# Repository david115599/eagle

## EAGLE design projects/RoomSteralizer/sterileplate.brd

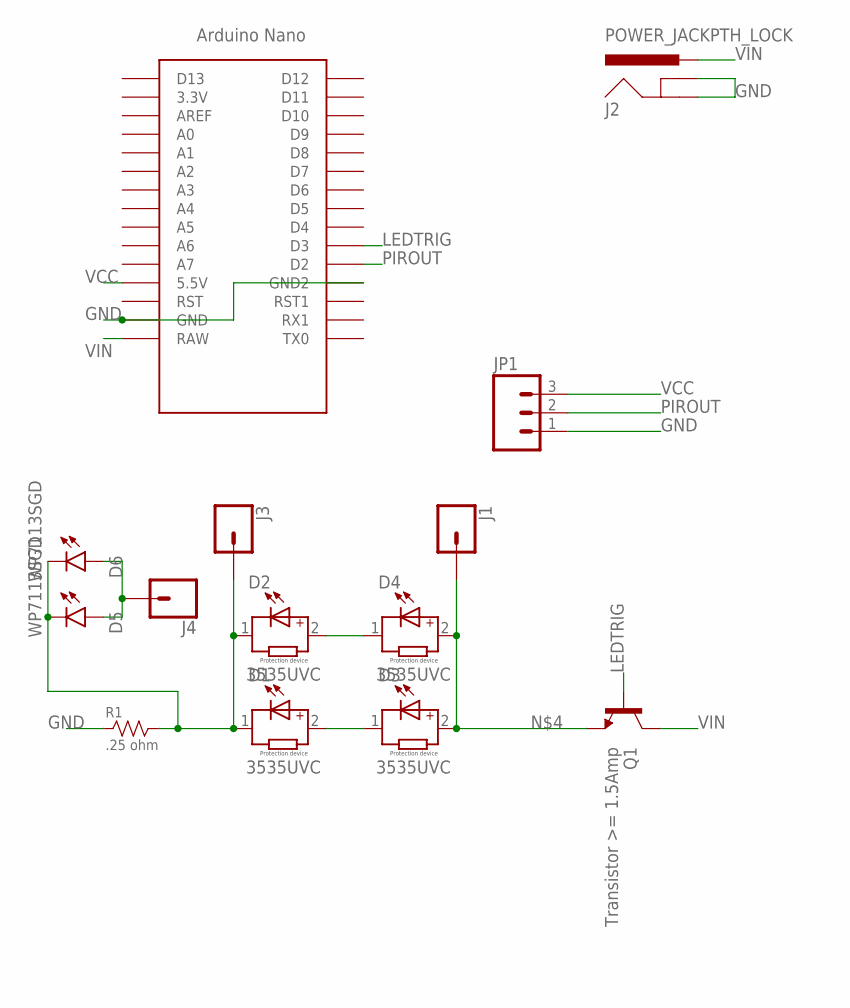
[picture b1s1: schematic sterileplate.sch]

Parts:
D1, D2, D3, D4: 3535UVC; WL-SWTC_3535
D5, D6: WP7113SGD; RADIAL_5MM
J1, J3, J4: CONN_01PTH_2MM; 1X01_2MM
J2: POWER_JACKPTH_LOCK; POWER_JACK_PTH_LOCK; MPN DCJ235-05-A-K1-K
JP1: M03PTH; 1X03
Q1: Transistor >= 1.5Amp; TO-92
R1: .25 ohm; AXL-REGULAR
U$1: NANO

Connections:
GND: J2.GND, J2.GNDBREAK, JP1.1, R1.1, U$1.GND, U$1.GND1 (GND2)
LEDTRIG: Q1.2 (B), U$1.D3
unnamed: D2.2, D4.1
unnamed: D1.2, D3.1
unnamed: D3.2, D4.2, J1.1, Q1.1 (E)
unnamed: D5.A, D6.A, J4.1
unnamed: D1.1, D2.1, D5.C, D6.C, J3.1, R1.2
PIROUT: JP1.2, U$1.D2
VCC: JP1.3, U$1.5V (5.5V)
VIN: J2.PWR, Q1.3 (C), U$1.RAW

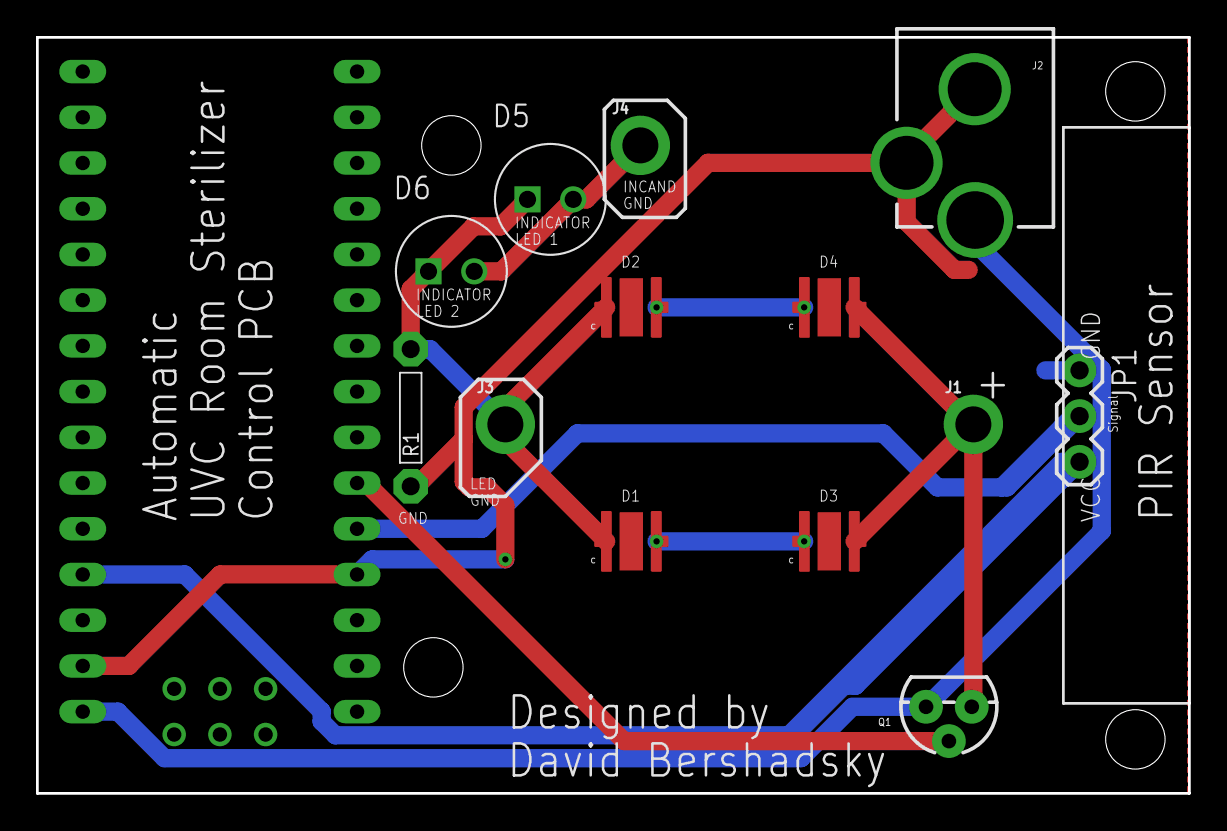
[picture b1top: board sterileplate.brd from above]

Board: 2 copper layers, 64.0 x 42.0 mm, 14 parts (0 on the bottom side), 10 nets.

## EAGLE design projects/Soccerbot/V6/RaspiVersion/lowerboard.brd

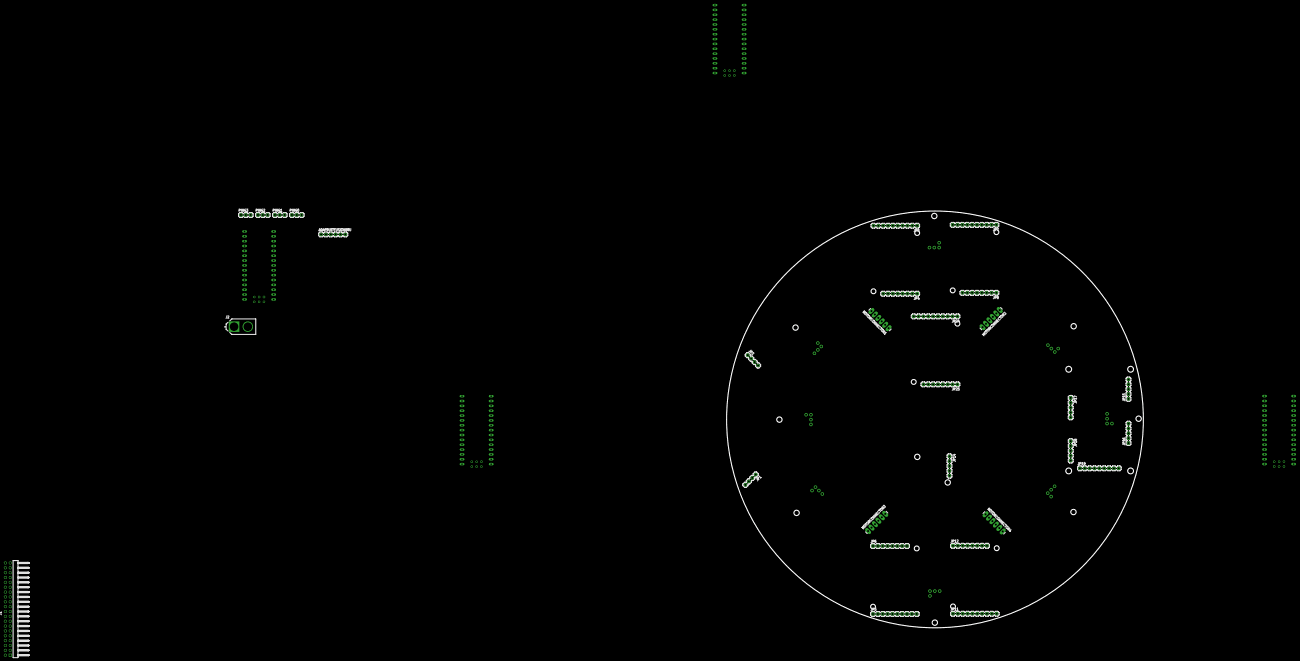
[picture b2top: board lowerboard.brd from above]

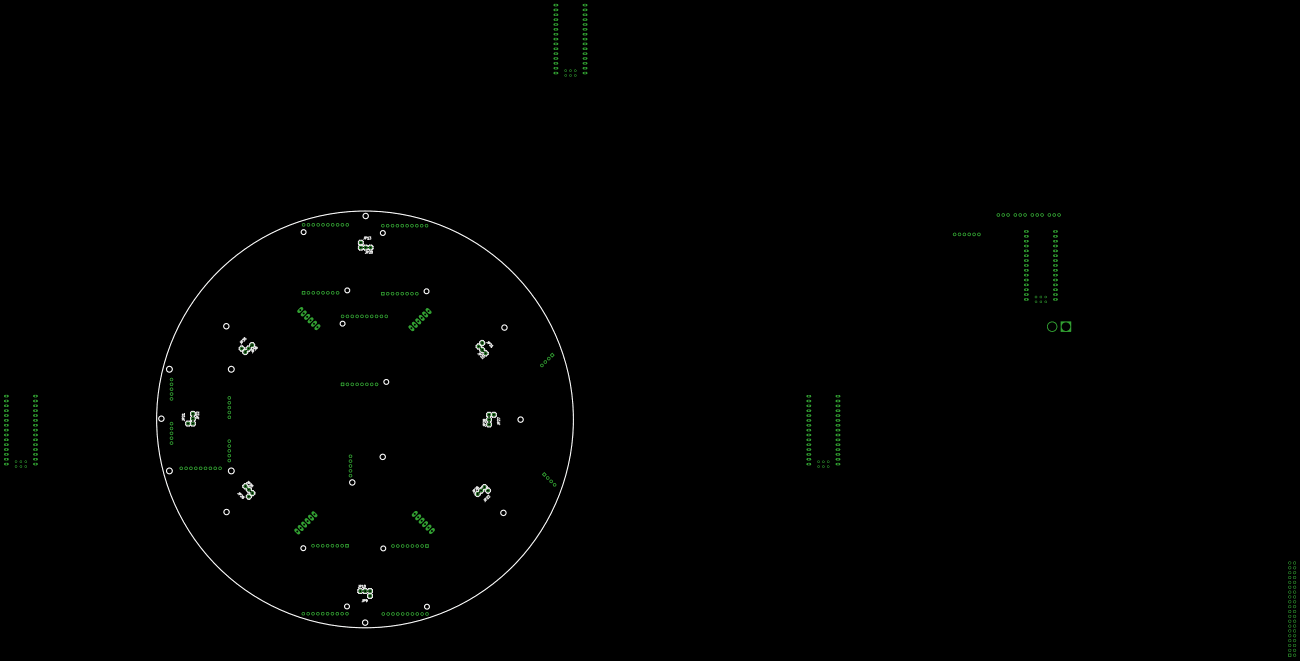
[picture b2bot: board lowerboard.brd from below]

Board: 2 copper layers, 218.0 x 218.0 mm, 49 parts (16 on the bottom side), 46 nets, no tracks yet.

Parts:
ADAFRUITFUSIONIMU: 1X06
J1: 61304021021
J2: XT60-M; AMASS_XT60-M
JP1, JP2: 1X04
JP3, JP5, JP7, JP11, JP24: M10"; 1X10
JP4, JP6, JP8, JP12, JP25: 1X08
JP9, JP13, JP21, JP23, JP27, JP29, JP31, JP35: M01PTH; 1X01
JP10, JP20, JP22, JP26, JP28, JP30, JP32, JP36: 1X03
JP14, JP15, JP16, JP17, JP18: 1X05
JP19: M09; 1X09
MOTORCONNECTOR1, MOTORCONNECTOR2, MOTORCONNECTOR3, MOTORCONNECTOR4: 1X06_LONGPADS
PING0, PING1, PING2, PING3: 1X03
U$1, U$2, U$3, U$6: NANO

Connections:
5V: JP1.4, JP2.4, JP3.7, JP5.7, JP7.7, JP10.2, JP11.7, JP14.1, JP19.8, JP20.2, JP22.2, JP24.7, JP26.2, JP28.2, JP30.2, JP32.2, JP36.2, MOTORCONNECTOR1.3, MOTORCONNECTOR2.3, MOTORCONNECTOR3.3, MOTORCONNECTOR4.3
CTRL: JP9.1, JP13.1, JP21.1, JP23.1, JP27.1, JP29.1, JP31.1, JP35.1, U$2.D2
ENCCS1: JP19.4, U$1.D2
ENCCS2: JP19.3, U$1.D3
ENCCS3: JP19.2, U$1.D4
ENCCS4: JP19.1, U$1.D5
ENCMISO: JP19.6, U$1.D12
ENCMOSI: JP19.5, U$1.D11
ENCSCLK: JP19.7, U$1.D13
GND: ADAFRUITFUSIONIMU.3, J1.5, J1.13, J1.20, J1.24, J1.26, J1.31, J1.34, J1.38, J2.1, JP1.3, JP2.3, JP3.8, JP3.10, JP4.5, JP4.6, JP5.8, JP5.10, JP6.5, JP6.6, JP7.8, JP7.10, JP8.5, JP8.6, JP10.3, JP11.8, JP11.10, JP12.5, JP12.6, JP14.2, JP14.3, JP19.9, JP20.3, JP22.3, JP24.8, JP24.10, JP25.5, JP25.6, JP26.3, JP28.3, JP30.3, JP32.3, JP36.3, MOTORCONNECTOR1.4, MOTORCONNECTOR2.4, MOTORCONNECTOR3.4, MOTORCONNECTOR4.4, PING0.1, PING1.1, PING2.1, PING3.1, U$1.GND, U$1.GND1, U$2.GND, U$2.GND1, U$3.GND, U$3.GND1, U$6.GND, U$6.GND1
INA0: JP3.1, U$6.D3
INA1: JP7.1, U$6.D7
INA2: JP5.1, U$6.D12
INA3: JP11.1, U$6.A0
INA4: JP24.1, U$6.A2
INB0: JP3.6, U$6.D4
INB1: JP7.6, U$6.D8
INB2: JP5.6, U$6.D13
INB3: JP11.6, U$6.A1
INB4: JP24.6, U$6.A3
OUTA0: JP4.1, JP4.2
OUTA1: JP8.1, JP8.2
OUTA2: JP6.1, JP6.2
OUTA3: JP12.1, JP12.2
OUTA4: JP25.1, JP25.2
OUTB0: JP4.3, JP4.4
OUTB1: JP8.3, JP8.4
OUTB2: JP6.3, JP6.4
OUTB3: JP12.3, JP12.4
OUTB4: JP25.3, JP25.4
PING0: PING0.3, U$2.A0
PING1: PING1.3, U$2.A1
PING2: PING2.3, U$2.A2
PING3: PING3.3, U$2.A3
SCLTOF: JP1.2, JP2.2, U$1.A5
SDATOF: JP1.1, JP2.1, U$1.A4
SO1: JP30.1, U$2.D3
SO2: JP22.1, U$2.D4
SO3: JP36.1, U$2.D5
SO4: JP20.1, U$2.D6
SO5: JP32.1, U$2.D7
SO6: JP28.1, U$2.D8
SO7: JP26.1, U$2.D9
VCC: ADAFRUITFUSIONIMU.1, J1.39, J1.40, PING0.2, PING1.2, PING2.2, PING3.2, U$1.5V, U$2.5V, U$3.5V, U$6.5V
VCC3.3: J1.1, J1.9, U$1.3.3V, U$2.3.3V, U$3.3.3V, U$6.3.3V
VIN: J2.2, JP4.7, JP4.8, JP6.7, JP6.8, JP8.7, JP8.8, JP12.7, JP12.8, JP14.4, JP25.7, JP25.8

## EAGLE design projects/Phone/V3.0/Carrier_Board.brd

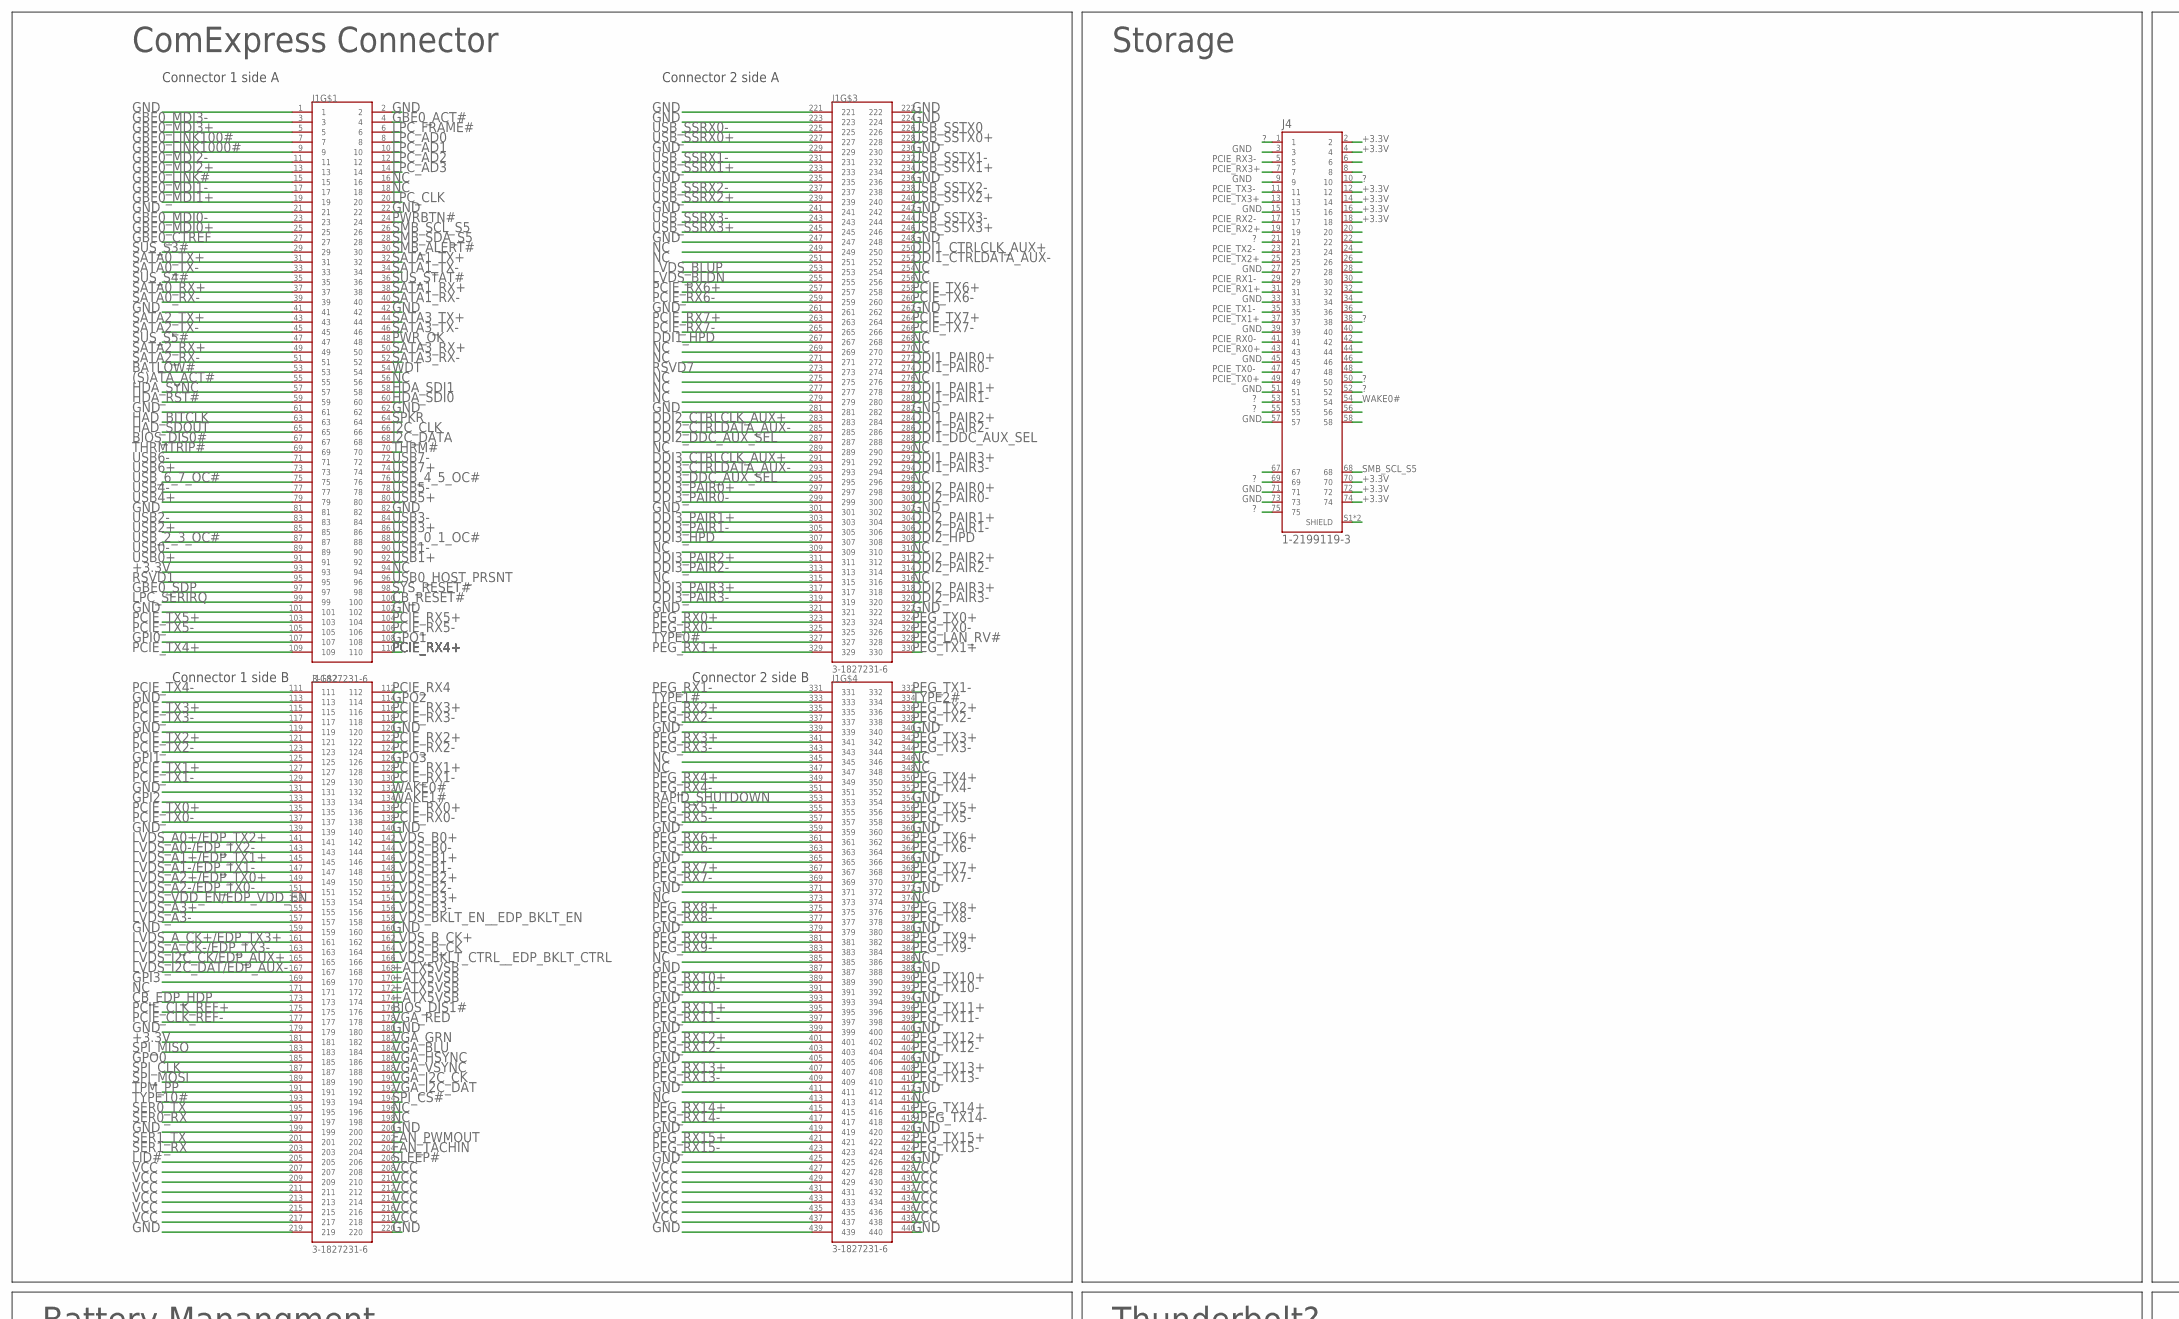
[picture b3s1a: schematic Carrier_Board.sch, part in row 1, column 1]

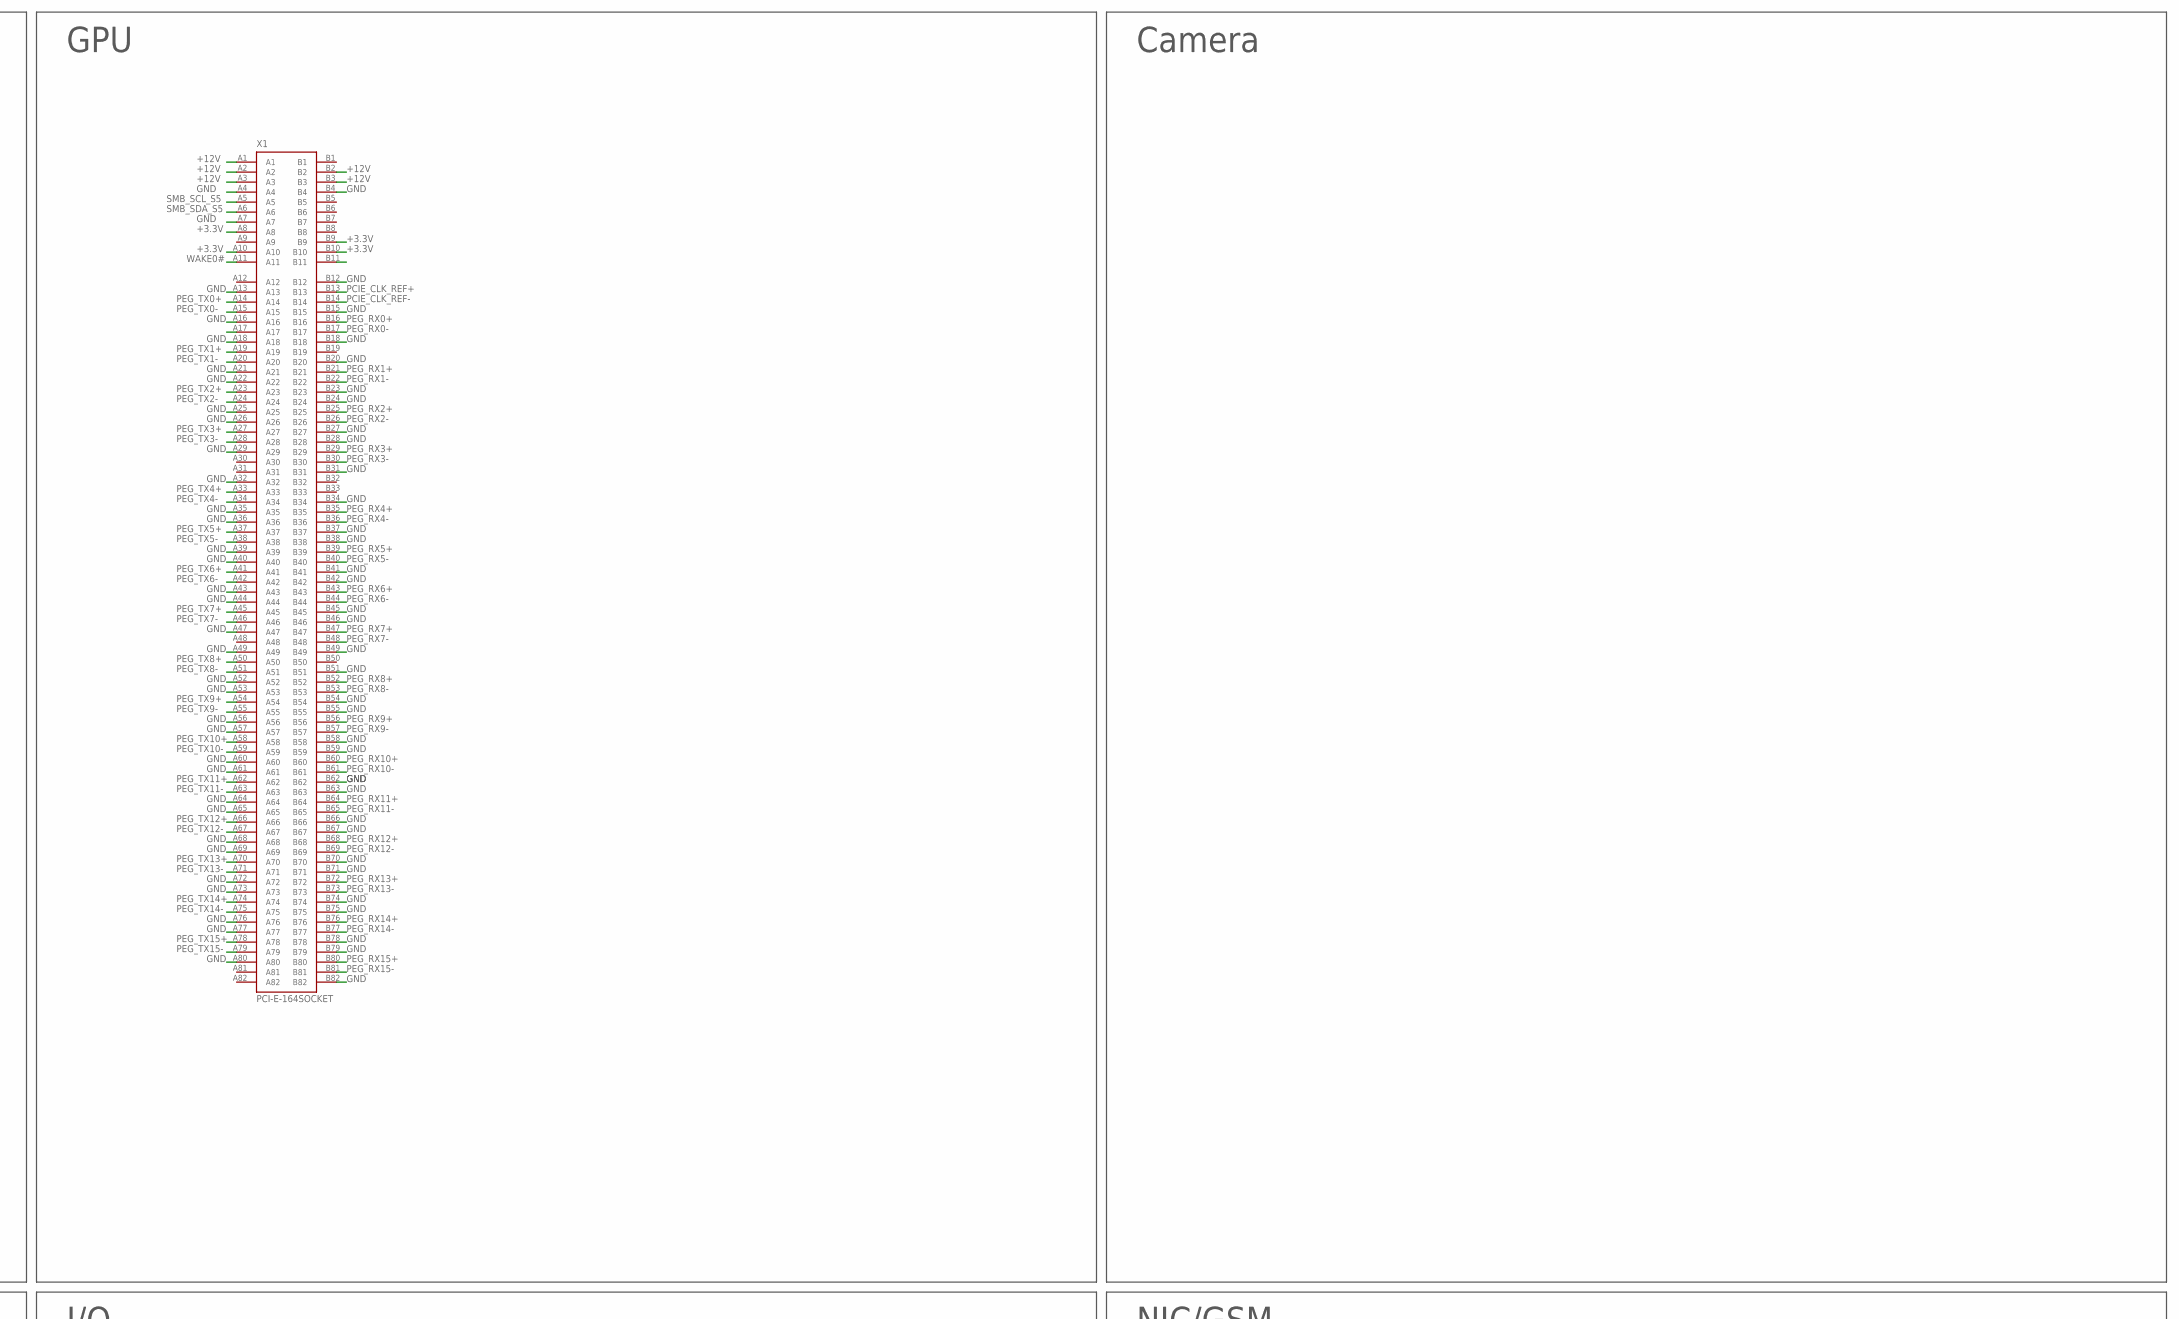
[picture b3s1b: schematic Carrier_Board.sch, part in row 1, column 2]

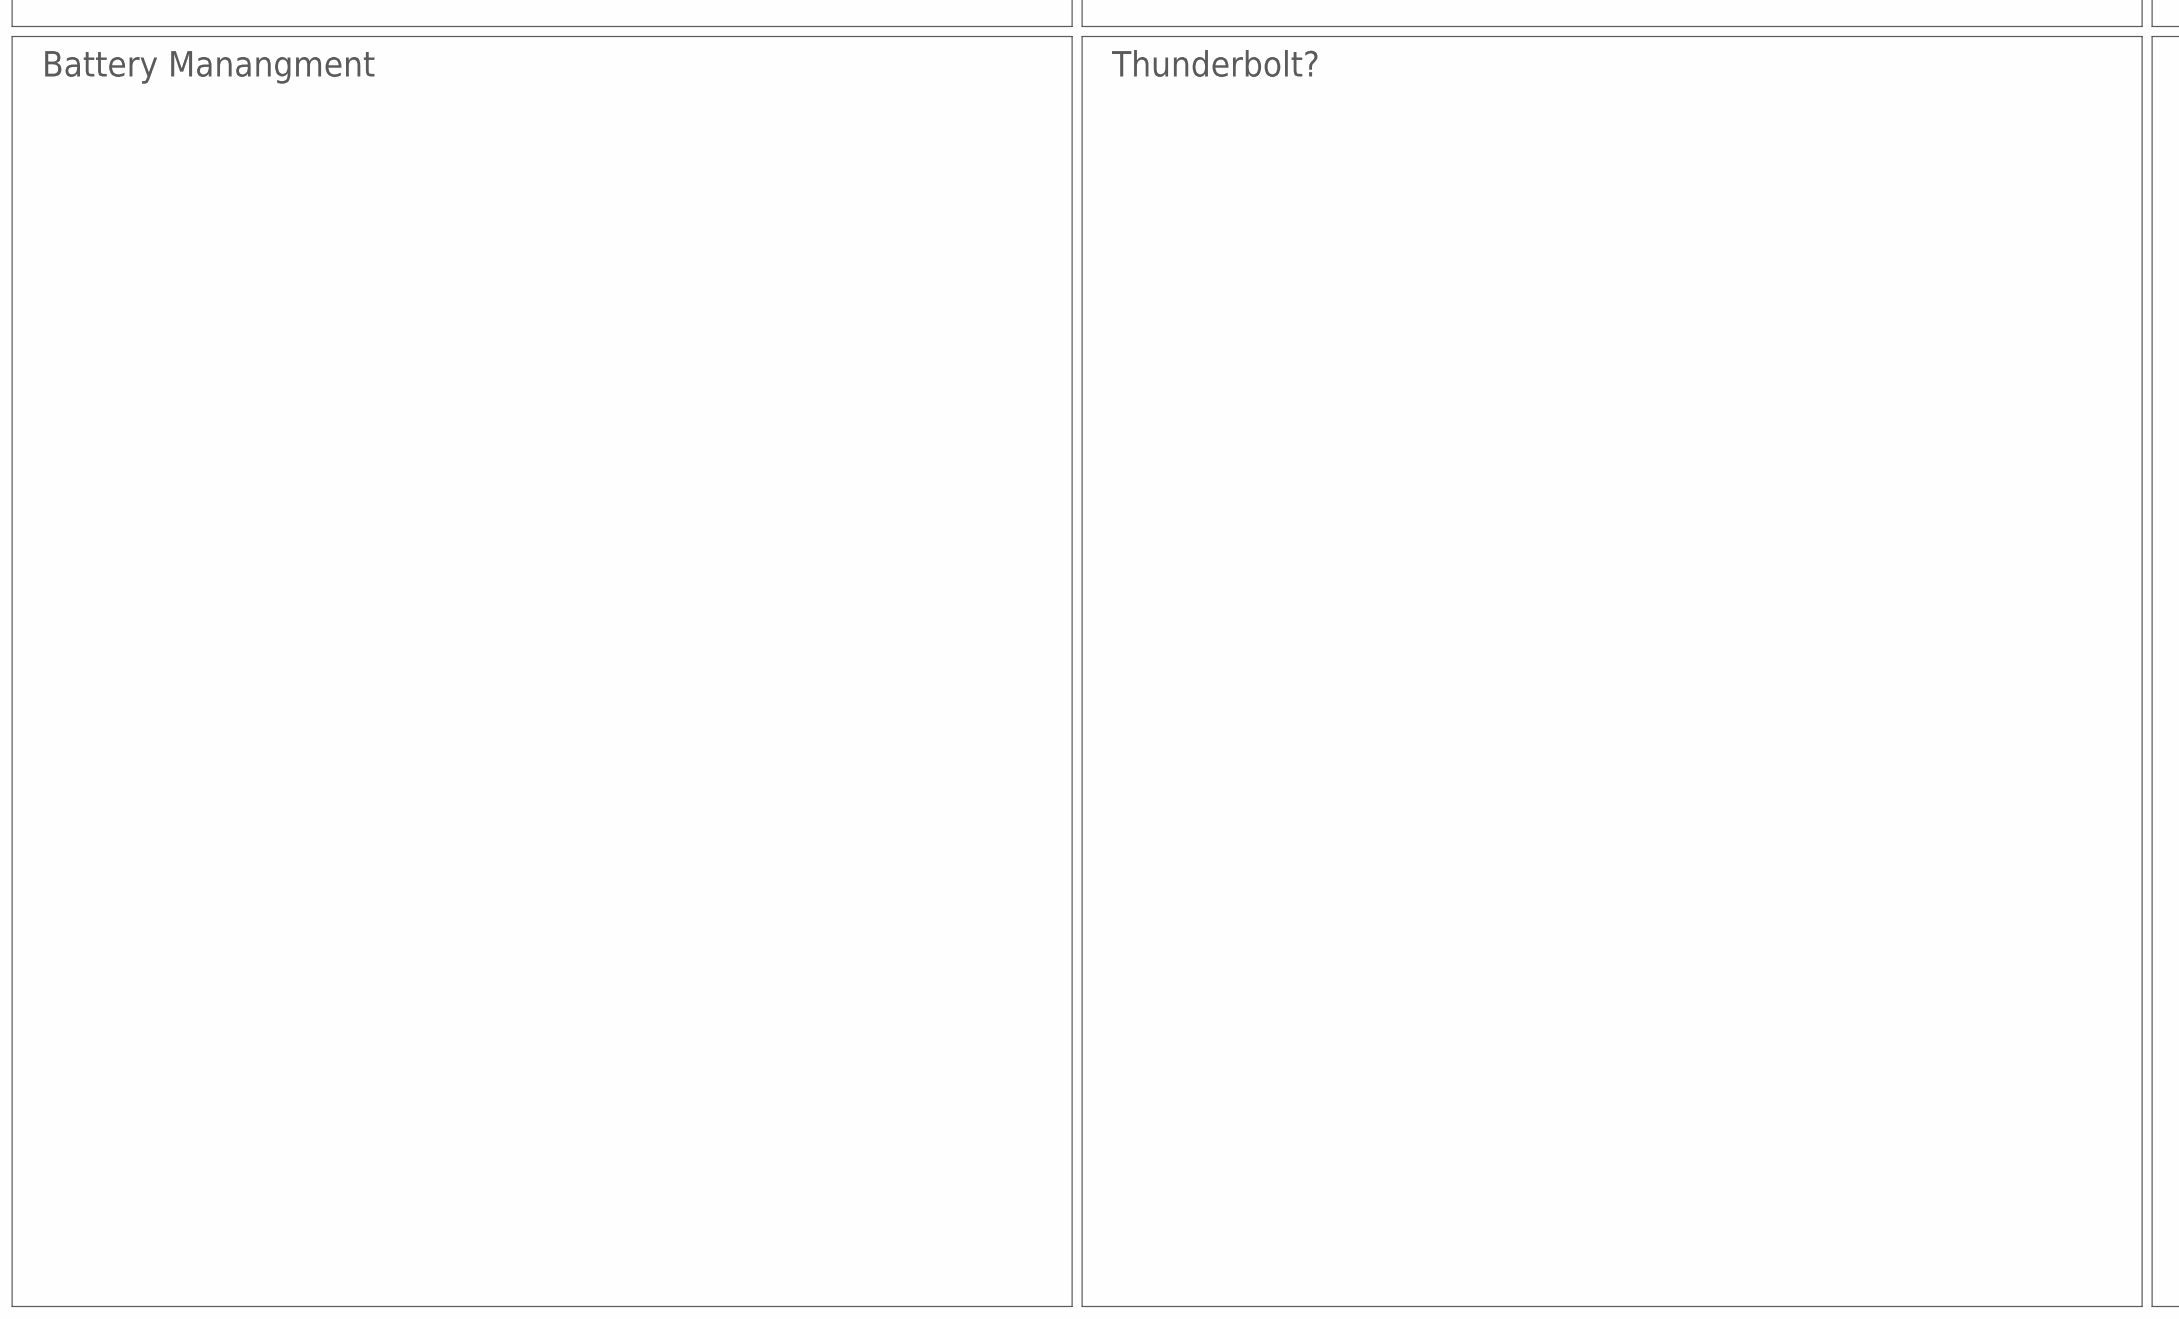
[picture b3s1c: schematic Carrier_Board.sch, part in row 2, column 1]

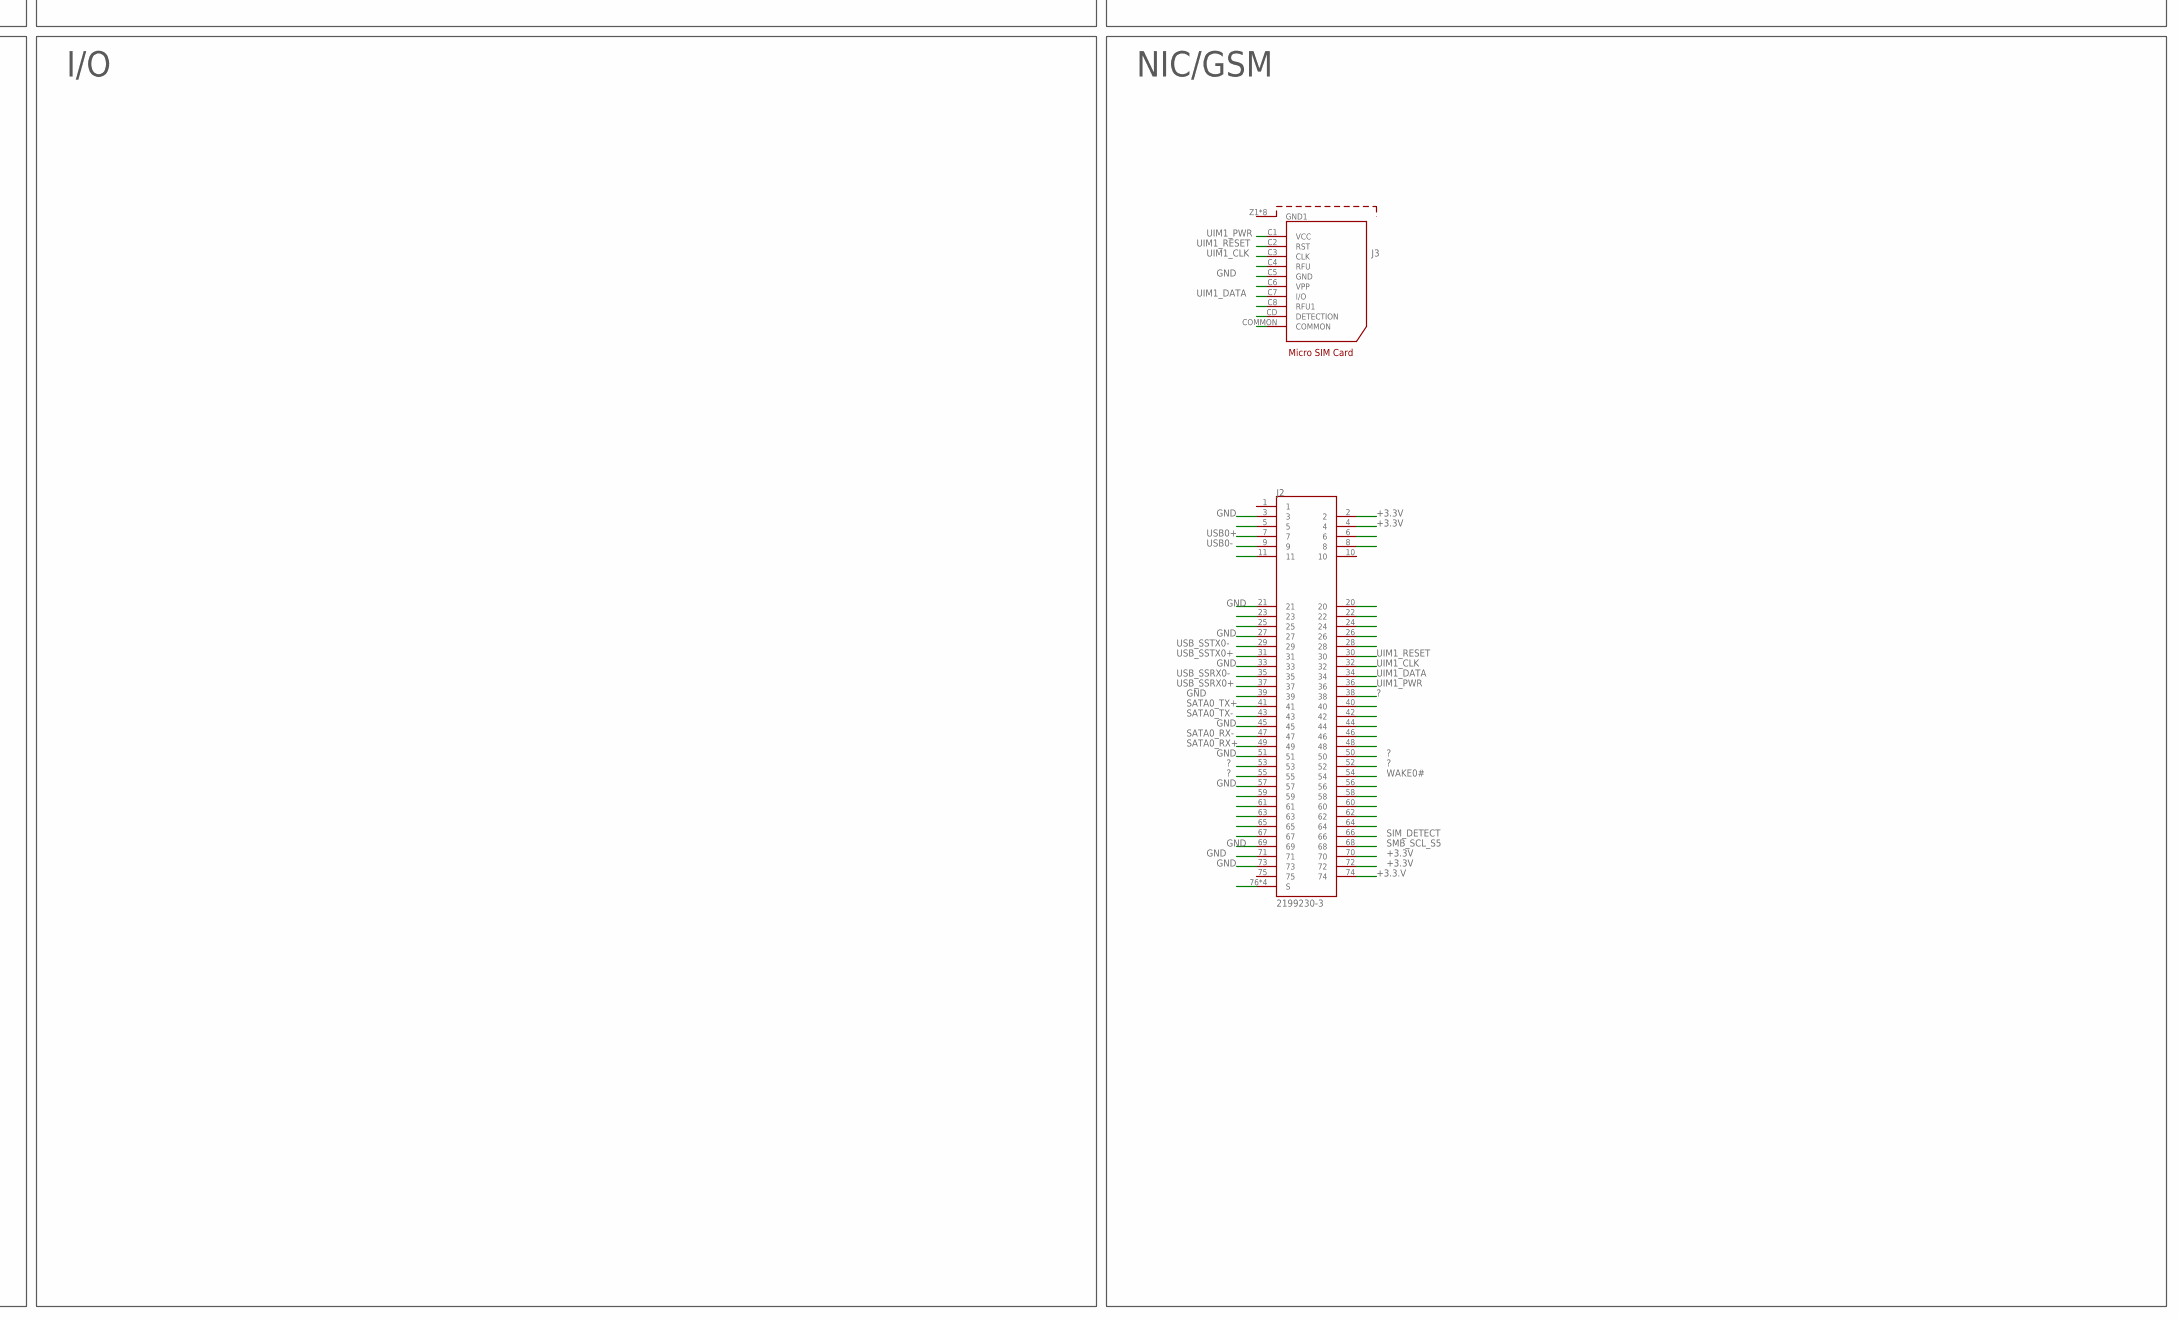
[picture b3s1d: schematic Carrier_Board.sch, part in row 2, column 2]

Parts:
J1: 3-1827231-6; TE_3-1827231-6
J2: 2199230-3; TE_2199230-3
J3: 693021010811
J4: 1-2199119-3; TE_1-2199119-3
X1: PCI-E-164SOCKET; PCI-E-164

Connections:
9PEG_TX14-: J1.418
(S)ATA_ACT#: J1.55
+3.3.V: J2.74
+3.3V: J1.93, J1.181, J2.2, J2.4, J2.70, J2.72, J4.2, J4.4, J4.12, J4.14, J4.16, J4.18, J4.70, J4.72, J4.74, X1.A8, X1.A10, X1.B9, X1.B10
+12V: X1.A1, X1.A2, X1.A3, X1.B2, X1.B3
+ATX5VSB: J1.168, J1.170, J1.172, J1.174
?: J2.38, J2.50, J2.52, J2.53, J2.55, J4.1, J4.10, J4.21, J4.38, J4.50, J4.52, J4.53, J4.55, J4.56, J4.69, J4.75
BATLOW#: J1.53
BIOS_DIS0#: J1.67
BIOS_DIS1#: J1.176
CB_EDP_HDP: J1.173
CB_RESET#: J1.100
DDI1_CTRLCLK_AUX+: J1.250
DDI1_CTRLDATA_AUX-: J1.252
DDI1_DDC_AUX_SEL: J1.288
DDI1_HPD: J1.267
DDI1_PAIR0+: J1.272
DDI1_PAIR0-: J1.274
DDI1_PAIR1+: J1.278
DDI1_PAIR1-: J1.280
DDI1_PAIR2+: J1.284
DDI1_PAIR2-: J1.286
DDI1_PAIR3+: J1.292
DDI1_PAIR3-: J1.294
DDI2_CTRLCLK_AUX+: J1.283
DDI2_CTRLDATA_AUX-: J1.285
DDI2_DDC_AUX_SEL: J1.287
DDI2_HPD: J1.308
DDI2_PAIR0+: J1.298
DDI2_PAIR0-: J1.300
DDI2_PAIR1+: J1.304
DDI2_PAIR1-: J1.306
DDI2_PAIR2+: J1.312
DDI2_PAIR2-: J1.314
DDI2_PAIR3+: J1.318
DDI2_PAIR3-: J1.320
DDI3_CTRLCLK_AUX+: J1.291
DDI3_CTRLDATA_AUX-: J1.293
DDI3_DDC_AUX_SEL: J1.295
DDI3_HPD: J1.307
DDI3_PAIR0+: J1.297
DDI3_PAIR0-: J1.299
DDI3_PAIR1+: J1.303
DDI3_PAIR1-: J1.305
DDI3_PAIR2+: J1.311
DDI3_PAIR2-: J1.313
DDI3_PAIR3+: J1.317
DDI3_PAIR3-: J1.319
FAN_PWMOUT: J1.202
FAN_TACHIN: J1.204
GBE0_ACT#: J1.4
GBE0_CTREF: J1.27
GBE0_LINK100#: J1.7
GBE0_LINK1000#: J1.9
GBE0_LINK#: J1.15
GBE0_MDI0+: J1.25
GBE0_MDI0-: J1.23
GBE0_MDI1+: J1.19
GBE0_MDI1-: J1.17
GBE0_MDI2+: J1.13
GBE0_MDI2-: J1.11
GBE0_MDI3+: J1.5
GBE0_MDI3-: J1.3
GBE0_SDP: J1.97
GND: J1.1, J1.2, J1.21, J1.22, J1.41, J1.42, J1.61, J1.62, J1.81, J1.82, J1.101, J1.102, J1.113, J1.119, J1.120, J1.131, J1.139, J1.140, J1.159, J1.160, J1.179, J1.180, J1.199, J1.200, J1.219, J1.220, J1.221, J1.222, J1.223, J1.224, J1.229, J1.230, J1.235, J1.236, J1.241, J1.242, J1.247, J1.248, J1.261, J1.262, J1.281, J1.282, J1.301, J1.302, J1.321, J1.322, J1.339, J1.340, J1.354, J1.359, J1.360, J1.365, J1.366, J1.371, J1.372, J1.379, J1.380, J1.387, J1.388, J1.393, J1.394, J1.399, J1.400, J1.405, J1.406, J1.411, J1.412, J1.419, J1.420, J1.425, J1.426, J1.439, J1.440, J2.3, J2.21, J2.27, J2.33, J2.39, J2.45, J2.51, J2.57, J2.69, J2.71, J2.73, J3.C5 (GND), J4.3, J4.9, J4.15, J4.27, J4.33, J4.39, J4.45, J4.51, J4.57, J4.71, J4.73, X1.A4, X1.A7, X1.A13, X1.A16, X1.A18, X1.A21, X1.A22, X1.A25, X1.A26, X1.A29, X1.A32, X1.A35, X1.A36, X1.A39, X1.A40, X1.A43, X1.A44, X1.A47, X1.A49, X1.A52, X1.A53, X1.A56, X1.A57, X1.A60, X1.A61, X1.A64, X1.A65, X1.A68, X1.A69, X1.A72, X1.A73, X1.A76, X1.A77, X1.A80, X1.B4, X1.B12, X1.B15, X1.B18, X1.B20, X1.B23, X1.B24, X1.B27, X1.B28, X1.B31, X1.B34, X1.B37, X1.B38, X1.B41, X1.B42, X1.B45, X1.B46, X1.B49, X1.B51, X1.B54, X1.B55, X1.B58, X1.B59, X1.B62, X1.B63, X1.B66, X1.B67, X1.B70, X1.B71, X1.B74, X1.B75, X1.B78, X1.B79, X1.B82
GPI0: J1.107
GPI1: J1.125
GPI2: J1.133
GPI3: J1.169
GPO0: J1.185
GPO1: J1.108
GPO2: J1.114
GPO3: J1.126
HAD_BITCLK: J1.63
HAD_SDOUT: J1.65
HDA_RST#: J1.59
HDA_SDI0: J1.60
HDA_SDI1: J1.58
HDA_SYNC: J1.57
I2C_CLK: J1.66
I2C_DATA: J1.68
LID#: J1.205
LPC_AD0: J1.8
LPC_AD1: J1.10
LPC_AD2: J1.12
LPC_AD3: J1.14
LPC_CLK: J1.20
LPC_FRAME#: J1.6
LPC_SERIRQ: J1.99
LVDS_A0+/EDP_TX2+: J1.141
LVDS_A0-/EDP_TX2-: J1.143
LVDS_A1+/EDP_TX1+: J1.145
LVDS_A1-/EDP_TX1-: J1.147
LVDS_A2+/EDP_TX0+: J1.149
LVDS_A2-/EDP_TX0-: J1.151
LVDS_A3+: J1.155
LVDS_A3-: J1.157
LVDS_A_CK+/EDP_TX3+: J1.161
LVDS_A_CK-/EDP_TX3-: J1.163
LVDS_B0+: J1.142
LVDS_B0-: J1.144
LVDS_B1+: J1.146
LVDS_B1-: J1.148
LVDS_B2+: J1.150
LVDS_B2-: J1.152
LVDS_B3+: J1.154
LVDS_B3-: J1.156
LVDS_BKLT_CTRL__EDP_BKLT_CTRL: J1.166
LVDS_BKLT_EN__EDP_BKLT_EN: J1.158
LVDS_BLDN: J1.255
LVDS_BLUP: J1.253
LVDS_B_CK: J1.164
LVDS_B_CK+: J1.162
LVDS_I2C_CK/EDP_AUX+: J1.165
LVDS_I2C_DAT/EDP_AUX-: J1.167
LVDS_VDD_EN/EDP_VDD_EN: J1.153
unnamed: J4.S1 (SHIELD), J4.S2 (SHIELD)
unnamed: J2.76 (S), J2.77 (S), J2.78 (S), J2.79 (S)
NC: J1.16, J1.18, J1.56, J1.94, J1.171, J1.196, J1.198, J1.249, J1.251, J1.254, J1.256, J1.268, J1.269, J1.270, J1.271, J1.275, J1.276, J1.277, J1.279, J1.289, J1.290, J1.296, J1.309, J1.310, J1.315, J1.316, J1.345, J1.346, J1.347, J1.348, J1.373, J1.374, J1.385, J1.386, J1.413, J1.414
PCIE_CLK_REF+: J1.175, X1.B13
PCIE_CLK_REF-: J1.177, X1.B14
PCIE_RX0+: J1.136, J4.43
PCIE_RX0-: J1.138, J4.41
PCIE_RX1+: J1.128, J4.31
PCIE_RX1-: J1.130, J4.29
PCIE_RX2+: J1.122, J4.19
PCIE_RX2-: J1.124, J4.17
PCIE_RX3+: J1.116, J4.7
PCIE_RX3-: J1.118, J4.5
PCIE_RX4: J1.112
PCIE_RX4+: J1.110
PCIE_RX5+: J1.104
PCIE_RX5-: J1.106
PCIE_RX6+: J1.257
PCIE_RX6-: J1.259
PCIE_RX7+: J1.263
PCIE_RX7-: J1.265
PCIE_TX0+: J1.135, J4.49
PCIE_TX0-: J1.137, J4.47
PCIE_TX1+: J1.127, J4.37
PCIE_TX1-: J1.129, J4.35
PCIE_TX2+: J1.121, J4.25
PCIE_TX2-: J1.123, J4.23
PCIE_TX3+: J1.115, J4.13
PCIE_TX3-: J1.117, J4.11
PCIE_TX4+: J1.109
PCIE_TX4-: J1.111
PCIE_TX5+: J1.103
PCIE_TX5-: J1.105
PCIE_TX6+: J1.258
PCIE_TX6-: J1.260
PCIE_TX7+: J1.264
PCIE_TX7-: J1.266
PEG_LAN_RV#: J1.328
PEG_RX0+: J1.323, X1.B16
PEG_RX0-: J1.325, X1.B17
PEG_RX1+: J1.329, X1.B21
PEG_RX1-: J1.331, X1.B22
PEG_RX2+: J1.335, X1.B25
PEG_RX2-: J1.337, X1.B26
PEG_RX3+: J1.341, X1.B29
PEG_RX3-: J1.343, X1.B30
PEG_RX4+: J1.349, X1.B35
PEG_RX4-: J1.351, X1.B36
PEG_RX5+: J1.355, X1.B39
PEG_RX5-: J1.357, X1.B40
PEG_RX6+: J1.361, X1.B43
PEG_RX6-: J1.363, X1.B44
PEG_RX7+: J1.367, X1.B47
PEG_RX7-: J1.369, X1.B48
PEG_RX8+: J1.375, X1.B52
PEG_RX8-: J1.377, X1.B53
PEG_RX9+: J1.381, X1.B56
PEG_RX9-: J1.383, X1.B57
PEG_RX10+: J1.389, X1.B60
PEG_RX10-: J1.391, X1.B61
PEG_RX11+: J1.395, X1.B64
PEG_RX11-: J1.397, X1.B65
PEG_RX12+: J1.401, X1.B68
PEG_RX12-: J1.403, X1.B69
PEG_RX13+: J1.407, X1.B72
PEG_RX13-: J1.409, X1.B73
PEG_RX14+: J1.415, X1.B76
PEG_RX14-: J1.417, X1.B77
PEG_RX15+: J1.421, X1.B80
PEG_RX15-: J1.423, X1.B81
PEG_TX0+: J1.324, X1.A14
PEG_TX0-: J1.326, X1.A15
PEG_TX1+: J1.330, X1.A19
PEG_TX1-: J1.332, X1.A20
PEG_TX2+: J1.336, X1.A23
PEG_TX2-: J1.338, X1.A24
PEG_TX3+: J1.342, X1.A27
PEG_TX3-: J1.344, X1.A28
PEG_TX4+: J1.350, X1.A33
PEG_TX4-: J1.352, X1.A34
PEG_TX5+: J1.356, X1.A37
PEG_TX5-: J1.358, X1.A38
PEG_TX6+: J1.362, X1.A41
PEG_TX6-: J1.364, X1.A42
PEG_TX7+: J1.368, X1.A45
PEG_TX7-: J1.370, X1.A46
PEG_TX8+: J1.376, X1.A50
PEG_TX8-: J1.378, X1.A51
PEG_TX9+: J1.382, X1.A54
PEG_TX9-: J1.384, X1.A55
PEG_TX10+: J1.390, X1.A58
PEG_TX10-: J1.392, X1.A59
PEG_TX11+: J1.396, X1.A62
PEG_TX11-: J1.398, X1.A63
PEG_TX12+: J1.402, X1.A66
PEG_TX12-: J1.404, X1.A67
PEG_TX13+: J1.408, X1.A70
PEG_TX13-: J1.410, X1.A71
PEG_TX14+: J1.416, X1.A74
PEG_TX14-: X1.A75
PEG_TX15+: J1.422, X1.A78
PEG_TX15-: J1.424, X1.A79
PWRBTN#: J1.24
PWR_OK: J1.48
RAPID_SHUTDOWN: J1.353
RSVD1: J1.95
RSVD7: J1.273
SATA0_RX+: J1.37, J2.49
SATA0_RX-: J1.39, J2.47
SATA0_TX+: J1.31, J2.41
SATA0_TX-: J1.33, J2.43
SATA1_RX+: J1.38
SATA1_RX-: J1.40
SATA1_TX+: J1.32
SATA1_TX-: J1.34
SATA2_RX+: J1.49
SATA2_RX-: J1.51
SATA2_TX+: J1.43
SATA2_TX-: J1.45
SATA3_RX+: J1.50
SATA3_RX-: J1.52
SATA3_TX+: J1.44
SATA3_TX-: J1.46
SER0_RX: J1.197
SER0_TX: J1.195
SER1_RX: J1.203
SER1_TX: J1.201
SIM_DETECT: J2.66
SLEEP#: J1.206
SMB_ALERT#: J1.30
SMB_SCL_S5: J1.26, J2.68, J4.68, X1.A5
SMB_SDA_S5: J1.28, X1.A6
SPI_CLK: J1.187
SPI_CS#: J1.194
SPI_MISO: J1.183
SPI_MOSI: J1.189
SPKR: J1.64
SUS_S3#: J1.29
SUS_S4#: J1.35
SUS_S5#: J1.47
SUS_STAT#: J1.36
SYS_RESET#: J1.98
THRM#: J1.70
THRMTRIP#: J1.69
TPM_PP: J1.191
TYPE0#: J1.327
TYPE1#: J1.333
TYPE2#: J1.334
TYPE10#: J1.193
UIM1_CLK: J2.32, J3.C3 (CLK)
UIM1_DATA: J2.34, J3.C7 (I/O)
UIM1_PWR: J2.36, J3.C1 (VCC)
UIM1_RESET: J2.30, J3.C2 (RST)
USB0+: J1.91, J2.7
USB0-: J1.89, J2.9
USB0_HOST_PRSNT: J1.96
USB1+: J1.92
USB1-: J1.90
USB2+: J1.85
USB2-: J1.83
USB3+: J1.86
USB3-: J1.84
USB4+: J1.79
USB4-: J1.77
USB5+: J1.80
USB5-: J1.78
USB6+: J1.73
USB6-: J1.71
USB7+: J1.74
USB7-: J1.72
USB_0_1_OC#: J1.88
USB_2_3_OC#: J1.87
USB_4_5_OC#: J1.76
USB_6_7_OC#: J1.75
USB_SSRX0+: J1.227, J2.37
USB_SSRX0-: J1.225, J2.35
USB_SSRX1+: J1.233
USB_SSRX1-: J1.231
USB_SSRX2+: J1.239
USB_SSRX2-: J1.237
USB_SSRX3+: J1.245
USB_SSRX3-: J1.243
USB_SSTX0: J1.226
USB_SSTX0+: J1.228, J2.5, J2.31
USB_SSTX0-: J2.29
USB_SSTX1+: J1.234
USB_SSTX1-: J1.232
USB_SSTX2+: J1.240
USB_SSTX2-: J1.238
USB_SSTX3+: J1.246
USB_SSTX3-: J1.244
VCC: J1.207, J1.208, J1.209, J1.210, J1.211, J1.212, J1.213, J1.214, J1.215, J1.216, J1.217, J1.218, J1.427, J1.428, J1.429, J1.430, J1.431, J1.432, J1.433, J1.434, J1.435, J1.436, J1.437, J1.438
VGA_BLU: J1.184
VGA_GRN: J1.182
VGA_HSYNC: J1.186
VGA_I2C_CK: J1.190
VGA_I2C_DAT: J1.192
VGA_RED: J1.178
VGA_VSYNC: J1.188
WAKE0#: J1.132, J2.54, J4.54, X1.A11
WAKE1#: J1.134
WDT: J1.54

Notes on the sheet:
ComExpress Connector
Connector 1 side A
Connector 2 side A
Connector 1 side B
Connector 2 side B
Storage
GPU
Battery Manangment
Thunderbolt?
I/O
Camera
NIC/GSM

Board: 2 copper layers, 5 parts (0 on the bottom side), 106 nets, no tracks yet.

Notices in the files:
parts and their libraries:
Wurth_Elektronik_Electromechanic_Input-O: Copyright: Würth Elektronik
FaBo-Coil: Released under the Creative Commons Attribution-ShareAlike 4.0 License
https://creativecommons.org/licenses/by-sa/4.0
